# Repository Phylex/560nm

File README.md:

# 560nm
Automated plant watering system

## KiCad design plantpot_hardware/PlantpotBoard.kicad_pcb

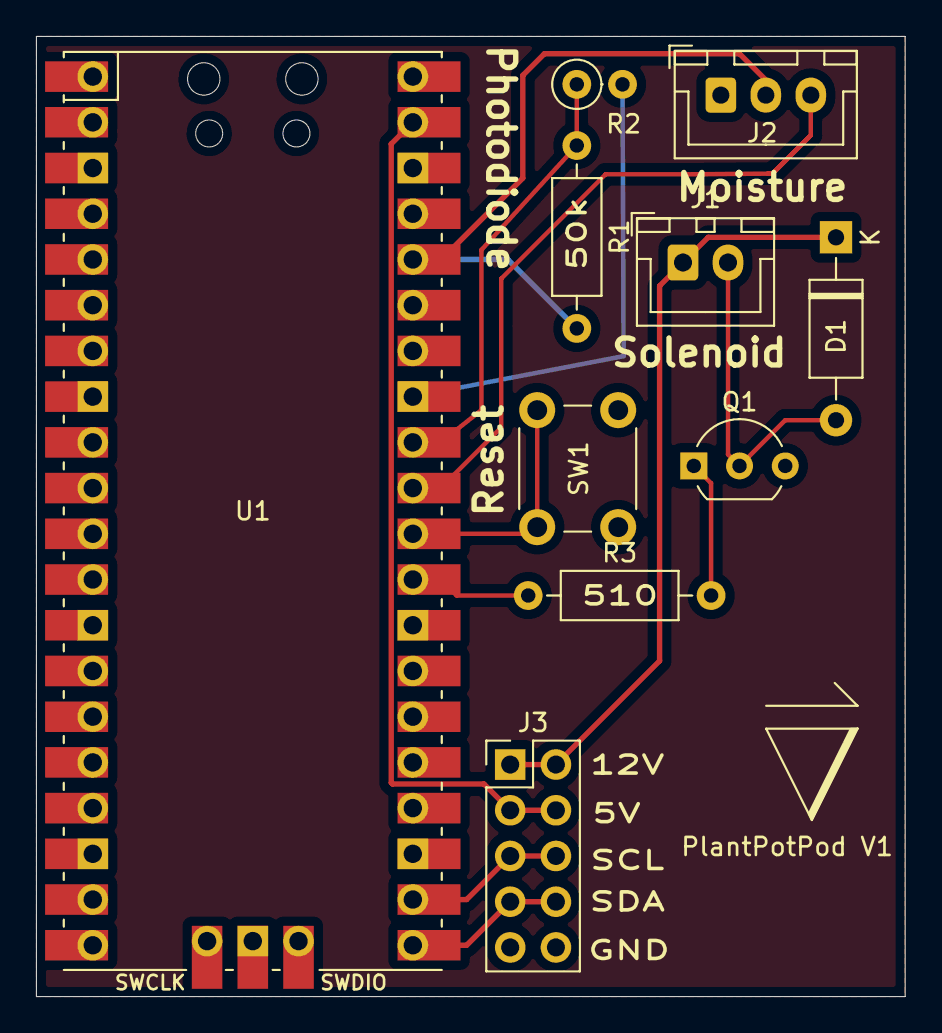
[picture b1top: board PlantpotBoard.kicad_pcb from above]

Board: 2 copper layers, 48.3 x 53.3 mm, 10 parts (0 on the bottom side), 13 nets.

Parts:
D1: 1N5817; D_A-405_P10.16mm_Horizontal
J1: Solenoid; JST_XH_B2B-XH-A_1x02_P2.50mm_Vertical
J2: Moisture Sensor; JST_XH_B3B-XH-A_1x03_P2.50mm_Vertical
J3: Bus Connector; PinHeader_2x05_P2.54mm_Vertical
Q1: BD135-16; TO-92_Inline_Wide
R1: 50k; R_Axial_DIN0207_L6.3mm_D2.5mm_P10.16mm_Horizontal
R2: 5k-200k; R_Axial_DIN0207_L6.3mm_D2.5mm_P2.54mm_Vertical
R3: 510; R_Axial_DIN0207_L6.3mm_D2.5mm_P10.16mm_Horizontal
SW1: reset; SW_PUSH_6mm
U1: Pico; RPi_Pico_SMD_TH

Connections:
+3V3: J2.2, R1.2, U1.36
+5V: J3.3, J3.4, U1.39
+12V: D1.1, J1.1, J3.1, J3.2
GND: J2.1, J3.9, J3.10, Q1.3, SW1.2, U1.38
GNDA: R2.2, U1.33
LIGHT: R1.1, R2.1, U1.32
MOIST: J2.3, U1.31
unnamed: D1.2, J1.2, Q1.2
unnamed: Q1.1, R3.2
unnamed: SW1.1, U1.30
SCL: J3.5, J3.6, U1.22
SDA: J3.7, J3.8, U1.21
Solenoid: R3.1, U1.29

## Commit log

2021-05-06 added the cmake file that includes the build system
2021-05-06 used code from tests as a starting point for firmware
2021-05-06 added in the build system cmake
2021-05-06 added dma for the adc
2021-05-06 fixed dma overrunn error
2021-05-08 added code to take 10000 measurements alternating between the brightness sensor and moisture sensor
2021-05-08 fixed an error I missed and changed the code to send the float vals over the i2c
2021-05-08 added the basic python boilerplate for the raspi client software
2021-05-09 got the code working
2021-05-09 added sample code that still needs testing
2021-05-09 changed minor problems with the python client
2021-05-09 some minor formatting tweaks
2021-05-09 fixed
2021-05-09 changed the adc rate to match the request speed
2021-05-16 changed the program to export prometheus metrics on port 8000
2021-05-16 removed print statements primarily used for debugging
2021-06-03 included library for the kicad model of the raspberry pi
2021-06-03 changed the pins so that nearly all of them are on one side
2021-06-03 cleaned up the file
2021-06-03 added kicad board project
2021-06-03 added loop so the client stays alive
2021-06-03 use flask to serve the metrics requests
2021-06-03 debugging
2021-06-04 added gitignore for the flask app
2021-06-04 moved the server into it's own directory
2021-06-12 added gerber files to the gitignore
2021-06-14 Added two classes that handle database integration of the plantpots
2021-06-14 added experimental files for testing the database
2021-06-14 testing round 1
2021-06-24 moved files around
2021-07-13 removed the old server and rewrote the server to run on aiohttp
2021-07-13 changed a small async error
2021-08-30 added files to gitignore
